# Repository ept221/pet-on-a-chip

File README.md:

# Pet On A Chip
Pet on a chip is a project which condenses the control logic the robot described in Frank DaCosta's book "How to Build Your Own Working Robot Pet" onto a single FPGA. More details, pictures, and videos can be found on this [blog post](https://ezrasrobots.wordpress.com/2021/07/07/pet-on-a-chip/).

## tinySoC
tinySoC is a small system on a chip responsible for controlling the robot. It consists of an 8-bit CPU, an 80 column VGA graphics controller, a programmable interrupt controller, GPIO, counter/timer peripherals, dual closed loop motor controllers, a servo controller, a sonar controller, and a UART, all implemented on an iCE40 FPGA. It also comes with an assembler and utilities for loading programs into the chip's internal block memory without having to rerun synthesis and place-and-route.

## The CPU

The CPU is an 8-bit RISC core, with a Harvard architecture. It has a 16-bit wide instruction memory, an 8-bit wide data memory, and both have a 16-bit address. The CPU has 16 general purpose 8-bit registers along with a 4-bit status register. The processor is not fully pipelined, but does fetch the next instruction while executing the current one. Most instructions execute in a single clock cycle, but a few take two or three.

## The GPU

The GPU operates in a monochrome 80 column text mode, and outputs a VGA signal at a resolution of 640 by 480 at 60 frames per second. The GPU contains an ASCII buffer which the user can write to in order to display messages on the screen. A control register allows the user to set the text to one of 7 colors, and to enable an interrupt to the CPU which fires every time a frame finishes and enters the blanking period. Not shown in the diagram is control logic that allows the screen to be scrolled upwards by writing to the control register.

## The Instruction Set

## The PCBs
The main board:

The expantion board:

## The Assembler

The assembler is case insensitive.

### Comments
Comments begin with semicolons.
```assembly
        .code
        ldi r0, 1 ; This is a comment
```

### Constants
Constants are in decimal by default, but hexadecimal and binary are also supported. Constants can also be negative and are stored in two's complement form when assembled. Chars can also be entered as constants.
```assembly
        .code
        ldi r0, 10     ; Decimal constant
        ldi r0, 0x0A   ; Hexadecimal constant
        ldi r0, 0b1010 ; Binary constant
        ldi r0, -10    ; A negative constant
        ldi r0, 'a'    ; A char constant
        ldi r0, '\n'   ; An escaped char constant
```

### Label Definitions
Label definitions may be any string ending with a colon, as long as the string is not in the form of a constant or is one of the reserved keywords

```assembly
        .code
        ldi r0, 10
loop:   adi r0, -1
        bnz loop
        hlt
```

### Directives

#### .code
Specifies that the following lines are code to be assembled and placed in instruction memory.

#### .data
Specifies that the following lines are data to be placed in data memory.

#### .org
Sets the origin to the given address. Only forward movement of the origin is permitted.
```assembly
        .code
        ldi r0, 1
        out r0, 0
        br foo
        
        .org 0x0B
foo:    out r0, 1
        hlt

;*************************************************************************
; Assembles to the following:
; Address        Label          Code                     Source
; ------------------------------------------------------------------------
; 0x0000                        0b0000000000010001       LDI R0, 1        
; 0x0001                        0b0000000000001001       OUT R0, 0        
; 0x0002                        0b0000000010011110       BR FOO           
; 0x000B         FOO:           0b0000000000011001       OUT R0, 1        
; 0x000C                        0b1111111111111111       HLT 
```

#### .db
Writes one or more data bytes sequentially into data memory.
```assembly
        .data
        .db 0x01, 0x44, 0x73

;*************************************************************************
; Assembles to the following:
; Address        Label          Data
; ------------------------------------------
; 0x0000                        0x01
; 0x0001                        0x44
; 0x0002                        0x73
```

#### .ds
Defines a block of space in the data memory. This is useful for allocating room for a buffer.
```assembly
        .data
        .db 5
        .ds 3
        .db 7

;*************************************************************************
; Assembles to the following:
; Address        Label          Data
; ------------------------------------------
; 0x0000                        0x05                                         
; 0x0004                        0x07 
```

#### .string
Writes a null terminated ASCII string into data memory. Double quotes and backslashes must be escaped with a backslash.

```assembly
        .data
        .string "The robot says \"Hi!\""
        
;*************************************************************************
; Assembles to the following:
; Address        Label          Data
; ------------------------------------------
; 0x0000                        0x54
; 0x0001                        0x68
; 0x0002                        0x65
; 0x0003                        0x20
; 0x0004                        0x72
; 0x0005                        0x6F
; 0x0006                        0x62
; 0x0007                        0x6F
; 0x0008                        0x74
; 0x0009                        0x20
; 0x000A                        0x73
; 0x000B                        0x61
; 0x000C                        0x79
; 0x000D                        0x73
; 0x000E                        0x20
; 0x000F                        0x22
; 0x0010                        0x48
; 0x0011                        0x69
; 0x0012                        0x21
; 0x0013                        0x22
; 0x0014                        0x00
```

#### .ostring
Write a ASCII string into data memory. The string is open, which means that it is not null terminated. This is useful if you have a long string that you want to split up into multiple lines in the assembly source file.

```assembly
        .data
        .ostring "Hi! "
        .string  "Bye!"

;*************************************************************************
; Assembles to the following:
; Address        Label          Data
; ------------------------------------------
; 0x0000                        0x48
; 0x0001                        0x69
; 0x0002                        0x21
; 0x0003                        0x20
; 0x0004                        0x42
; 0x0005                        0x79
; 0x0006                        0x65
; 0x0007                        0x21
; 0x0008                        0x00
```

#### .define
Equates a symbol with a number.
```assembly
        .code
        .define foo, 5
        ldi r0, foo
        hlt
        
;*************************************************************************
; Assembles to the following:        
; Address        Label          Code                     Source
; ------------------------------------------------------------------------
; 0x0000                        0b0000000001010001       LDI R0, FOO     
; 0x0001                        0b0000000011110000       HLT  
```

### Expressions
Any time an instruction or directive requires a numerical argument, an expression can be used.
Supported operations inside expressions include addition and subtraction. The location counter $ is also made available. If an instruction is two bytes long then $ refers to the address of the second byte. Expressions may contain symbols, but must resolve within two passes of the assembler, and if used for directive arguments, must resolve in a single pass.

```assembly
; Example resolution in one pass
        .code
        .define foo, 5
        ldi r0, foo + 7
        hlt

;*************************************************************************
; Assembles to the following:
; Address        Label          Code                     Source
; ------------------------------------------------------------------------
; 0x0000                        0b0000000011000001       LDI R0, FOO + 7
; 0x0001                        0b0000000011110000       HLT
```
```assembly
; Example resolution in two passes
        .code
        ldi r0, foo + 7
        hlt
        .define foo, 5

;*************************************************************************
; Assembles to the following:
; Address        Label          Code                     Source
; ------------------------------------------------------------------------
; 0x0000                        0b0000000011000001       LDI R0, FOO + 7
; 0x0001                        0b0000000011110000       HLT
```
```assembly
; Example resolution in two passes with $
        .code
        ldi r0, $
        jmp $ + foo
        .define foo, 2
        nop
        nop
        nop
        hlt

;*************************************************************************
; Assembles to the following:
; Address        Label          Code                     Source
; ------------------------------------------------------------------------
; 0x0000                        0b0000000000000001       LDI R0, $
; 0x0001                        0b0000000010111000       JMP $ + FOO
; 0x0002                        0b0000000000000100
; 0x0003                        0b0000000000000000       NOP
; 0x0004                        0b0000000000000000       NOP
; 0x0005                        0b0000000000000000       NOP
; 0x0006                        0b0000000011110000       HLT
```
## The Development Process
To perform synthesis and place-and-route, run:
```bash
make synth
make pnr
```
To assemble a demo program, run:
```bash
./assemble programs/shell.asm shell
```
To upload the configuration bitstream for the previously assembled program, run:
```bash
./upload shell
```
You will now be able to interact with a basic shell over the UART at 115200 baud. Additionally, the output will also be sent over the VGA interface.

## Requirements
- Yosys for synthisis
- nextpnr for place and route
- icestorm tools for icebram and iceprog

## Peripherals

There are a variety of memory mapped peripherals included in the system. The memory map is configured in `soc/src/d_ram_and_io/d_ram_and_io.v`. Currently addresses `0x0000` to `0x07FF` are mapped to data ram. The peripherals are mapped from `0x1000` to `0x10FF`. The instructions `in` and `out` are designed to allow for quickly and easily reading and writing to peripherals within this address range. For example, `out r1, 5` writes the value in r1 to address `0x1005`. In contrast, when reading and writing to data memory, or writing to the graphics buffer which is from `0x2000` to `0x2960`, `in` and `out` cannot be used, and the other load and store instructions must be used instead, which require setting up a pointer in a register pair to the memory location you want to operate on.

### GPIO
|Address|Register|r/w|Description|
|-------|--------|---|-----------|
|0x1000|Direction|r/w|Sets GPIO pins to input or output|
|0x1001|Port|r/w|Write values to be outputed|
|0x1002|Pin|r|Read values on pins|

### Counter Timer
|Address|Register|r/w|Description|
|-------|--------|---|-----------|
|0x1003| Scale LSB|r/w||
|0x1004| Scale MSB|r/w||
|0x1005| Control|r/w||
|0x1006| CMPR0|r/w||
|0x1007| CMPR1|r/w||
|0x1008| Counter|r||

### UART
|Address|Register|r/w|Description|
|-------|--------|---|-----------|
|0x1009| Baud|r/w| Configures the baudrate|
|0x100A| Status|r| Signals empty tx buffer and or full rx buffer|
|0x100B| Buffer |r/w| Write to tx buffer, read from rx buffer|

### Motor Controller
|Address|Register|r/w|Description|
|-------|--------|---|-----------|
|0x100C| Control |r/w| Sets the motors' directions|
|0x100D| Enable  |r/w| Enables the motor driver|
|0x100E| Speed 0 |r/w| Target speed of motor 0|
|0x100F| Speed 1 |r/w| Target speed of motor 1|
|0x1010| RPM 0 |r| Actual speed of motor 0|
|0x1011| RPM 1 |r| Actual speed of motor 1|

### Servo Controller
|Address|Register|r/w|Description|
|-------|--------|---|-----------|
|0x1012| Position|r/w| Sets the position of the servo|

### Sonar Controller
|Address|Register|r/w|Description|
|-------|--------|---|-----------|
|0x1013| Status | r| Signals new reading in range register |
|0x1014| Range | r| Holds the measured distance|

### Programmable Interrupt Controller
|Address|Register|r/w|Description|
|-------|--------|---|-----------|
|0x1015| Vect 0 Low|r/w| LSBs of interrupt vector 0|
|0x1016| Vect 0 High|r/w| MSBs of interrupt vector 0|
|0x1017| Vect 1 Low|r/w| LSBs of interrupt vector 1|
|0x1018| Vect 1 High|r/w| MSBs of interrupt vector 1|
|0x1019| Vect 2 Low|r/w| LSBs of interrupt vector 2|
|0x101A| Vect 2 High|r/w| MSBs of interrupt vector 2|
|0x101B| Vect 3 Low|r/w| LSBs of interrupt vector 3|
|0x101C| Vect 3 High|r/w| MSBs of interrupt vector 3|

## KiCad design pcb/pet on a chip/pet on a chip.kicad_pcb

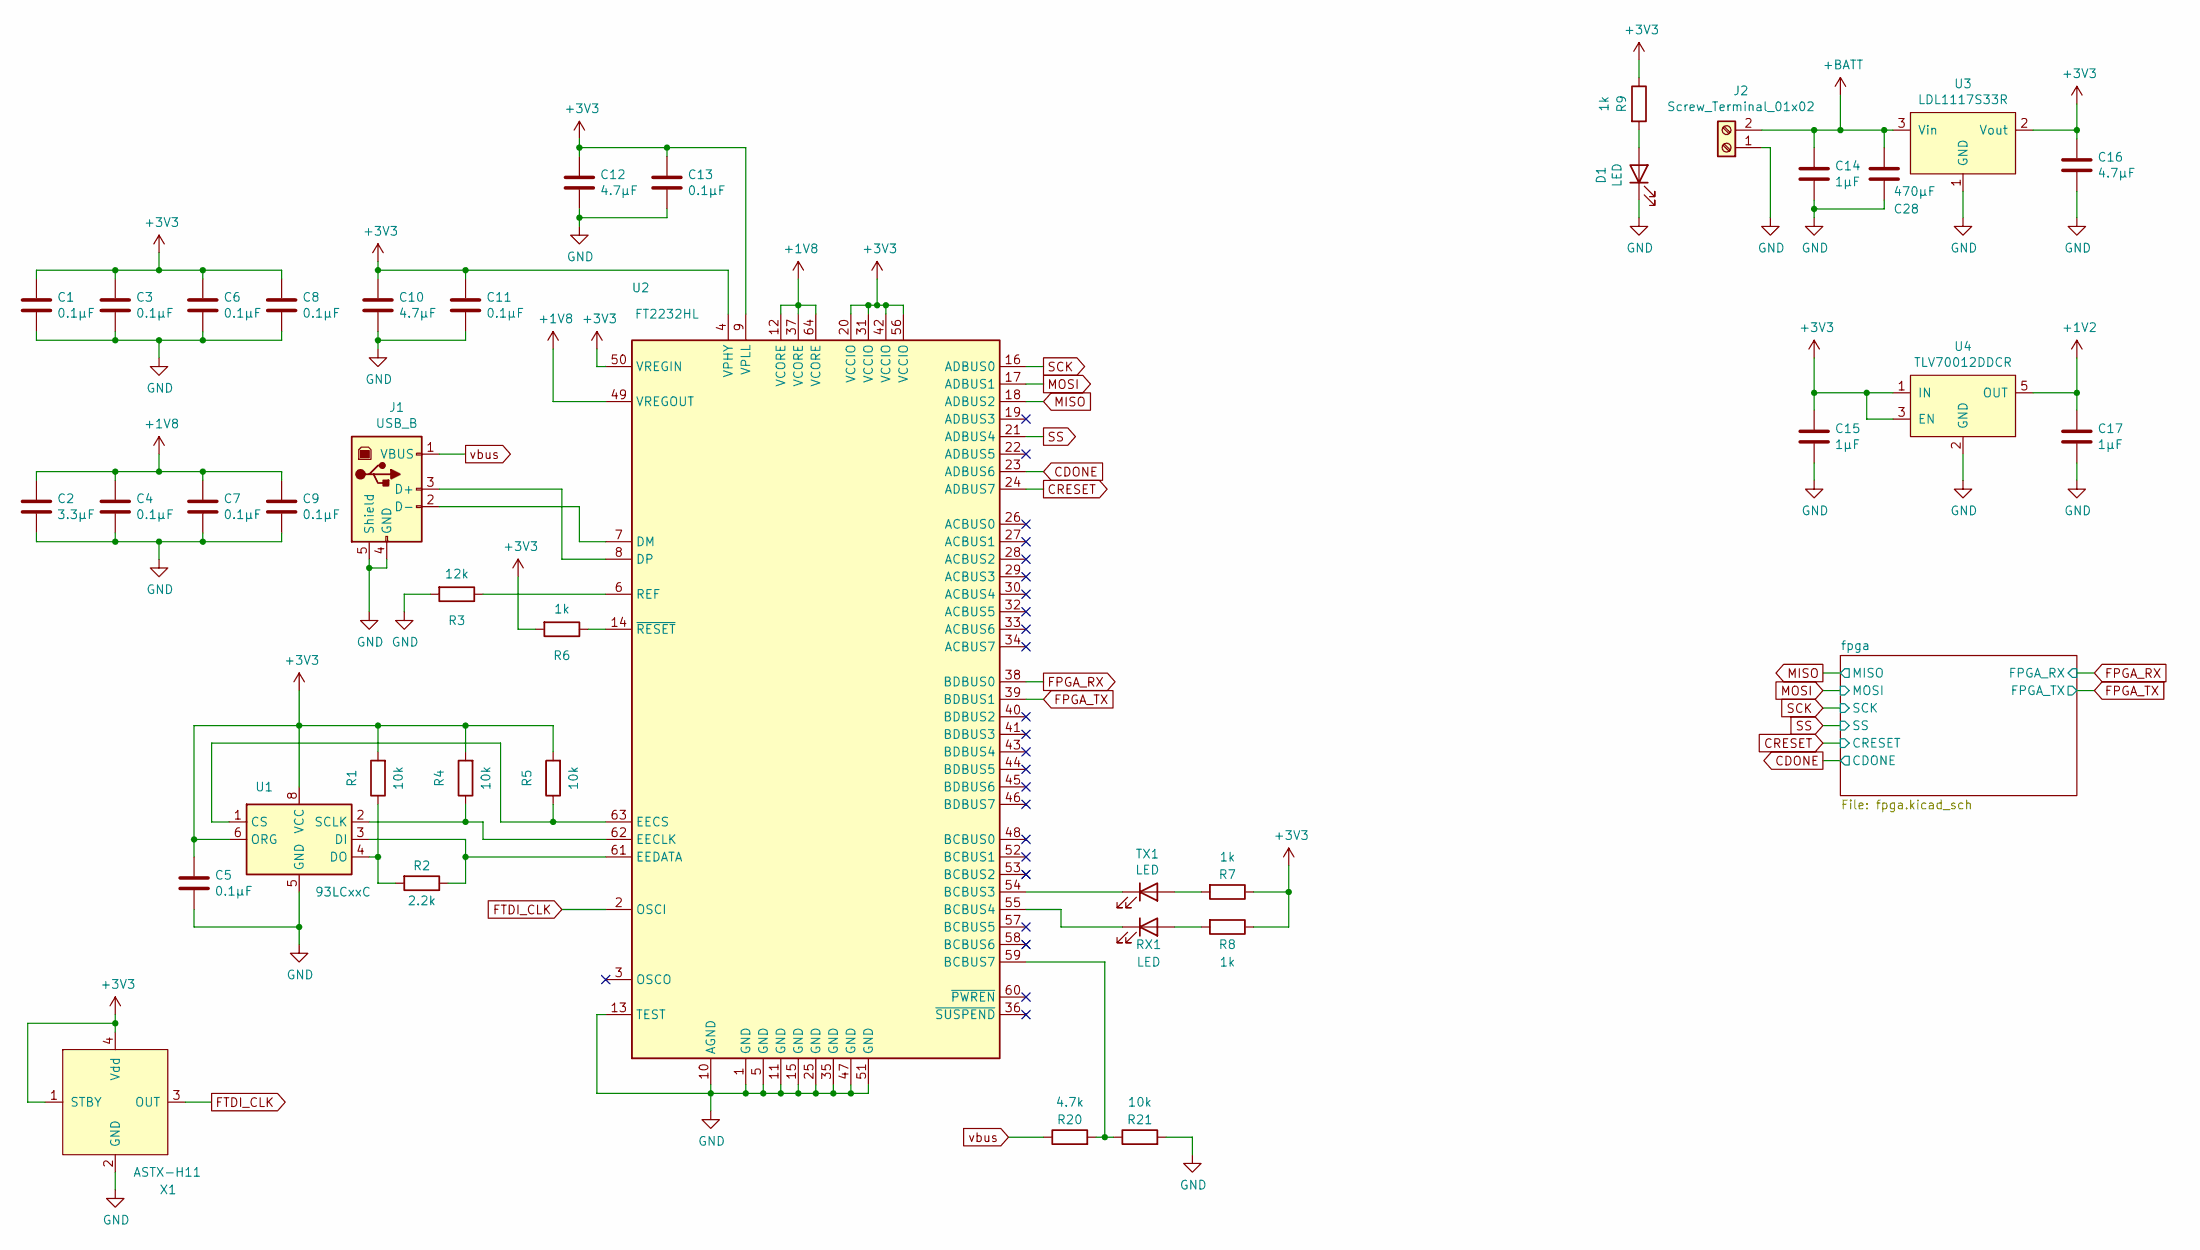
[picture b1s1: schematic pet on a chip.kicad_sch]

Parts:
C1, C3, C4, C5, C6, C7, C8, C9, C11, C13: 0.1µF; C_0603_1608Metric
C2: 3.3µF; C_0603_1608Metric
C10, C12, C16: 4.7µF; C_0603_1608Metric
C14, C15, C17: 1µF; C_0603_1608Metric
C28: 470µF; CP_Elec_6.3x7.7
D1: LED; R_0603_1608Metric
J1: USB_B; USB_B_OST_USB-B1HSxx_Horizontal
J2: Screw_Terminal_01x02; TerminalBlock_4Ucon_1x02_P3.50mm_Horizontal
R1, R4, R5, R21: 10k; R_0603_1608Metric
R2: 2.2k; R_0603_1608Metric
R3: 12k; R_0603_1608Metric
R6, R7, R8, R9: 1k; R_0603_1608Metric
R20: 4.7k; R_0603_1608Metric
RX1: LED; R_0603_1608Metric
TX1: LED; R_0603_1608Metric
U1: 93LCxxC; SOIC-8_3.9x4.9mm_P1.27mm
U2: FT2232HL; LQFP-64_10x10mm_P0.5mm
U3: LDL1117S33R; SOT-223-3_TabPin2
U4: TLV70012DDCR; SOT-23-5
X1: ASTX-H11; Oscillator_SMD_Abracon_ASE-4Pin_3.2x2.5mm

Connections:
+1V2: C17.1, U4.5 (OUT); also elsewhere on the board
+1V8: C2.1, C4.1, C7.1, C9.1, U2.12 (VCORE), U2.37 (VCORE), U2.49 (VREGOUT), U2.64 (VCORE)
+3V3: C1.1, C3.1, C5.1, C6.1, C8.1, C10.1, C11.1, C12.1, C13.1, C15.1, C16.1, R1.2, R4.2, R5.2, R6.2, R7.1, R8.1, R9.1, U1.6 (ORG), U1.8 (VCC), U2.4 (VPHY), U2.9 (VPLL), U2.20 (VCCIO), U2.31 (VCCIO), U2.42 (VCCIO), U2.50 (VREGIN), U2.56 (VCCIO), U3.2 (Vout), U4.1 (IN), U4.3 (EN), X1.1 (STBY), X1.4 (Vdd); also elsewhere on the board
+BATT: C14.1, C28.1, J2.2, U3.3 (Vin); also elsewhere on the board
CDONE: U2.23 (ADBUS6); also elsewhere on the board
CRESET: U2.24 (ADBUS7); also elsewhere on the board
FPGA_RX: U2.38 (BDBUS0); also elsewhere on the board
FPGA_TX: U2.39 (BDBUS1); also elsewhere on the board
FTDI_CLK: U2.2 (OSCI), X1.3 (OUT)
GND: C1.2, C2.2, C3.2, C4.2, C5.2, C6.2, C7.2, C8.2, C9.2, C10.2, C11.2, C12.2, C13.2, C14.2, C15.2, C16.2, C17.2, C28.2, D1.1 (K), J1.4 (GND), J1.5 (Shield), J2.1, R3.2, R21.2, U1.5 (GND), U2.1 (GND), U2.5 (GND), U2.10 (AGND), U2.11 (GND), U2.13 (TEST), U2.15 (GND), U2.25 (GND), U2.35 (GND), U2.47 (GND), U2.51 (GND), U3.1 (GND), U4.2 (GND), X1.2 (GND); also elsewhere on the board
MISO: U2.18 (ADBUS2); also elsewhere on the board
MOSI: U2.17 (ADBUS1); also elsewhere on the board
unnamed: D1.2 (A), R9.2
unnamed: J1.2 (D-), U2.7 (DM)
unnamed: J1.3 (D+), U2.8 (DP)
unnamed: R1.1, R2.2, U1.4 (DO)
unnamed: R2.1, U1.3 (DI), U2.61 (EEDATA)
unnamed: R3.1, U2.6 (REF)
unnamed: R4.1, U1.2 (SCLK), U2.62 (EECLK)
unnamed: R5.1, U1.1 (CS), U2.63 (EECS)
unnamed: R6.1, U2.14 (~RESET)
unnamed: R7.2, TX1.2 (A)
unnamed: R8.2, RX1.2 (A)
unnamed: R20.2, R21.1, U2.59 (BCBUS7)
unnamed: RX1.1 (K), U2.55 (BCBUS4)
unnamed: TX1.1 (K), U2.54 (BCBUS3)
SCK: U2.16 (ADBUS0); also elsewhere on the board
SS: U2.21 (ADBUS4); also elsewhere on the board
vbus: J1.1 (VBUS), R20.1

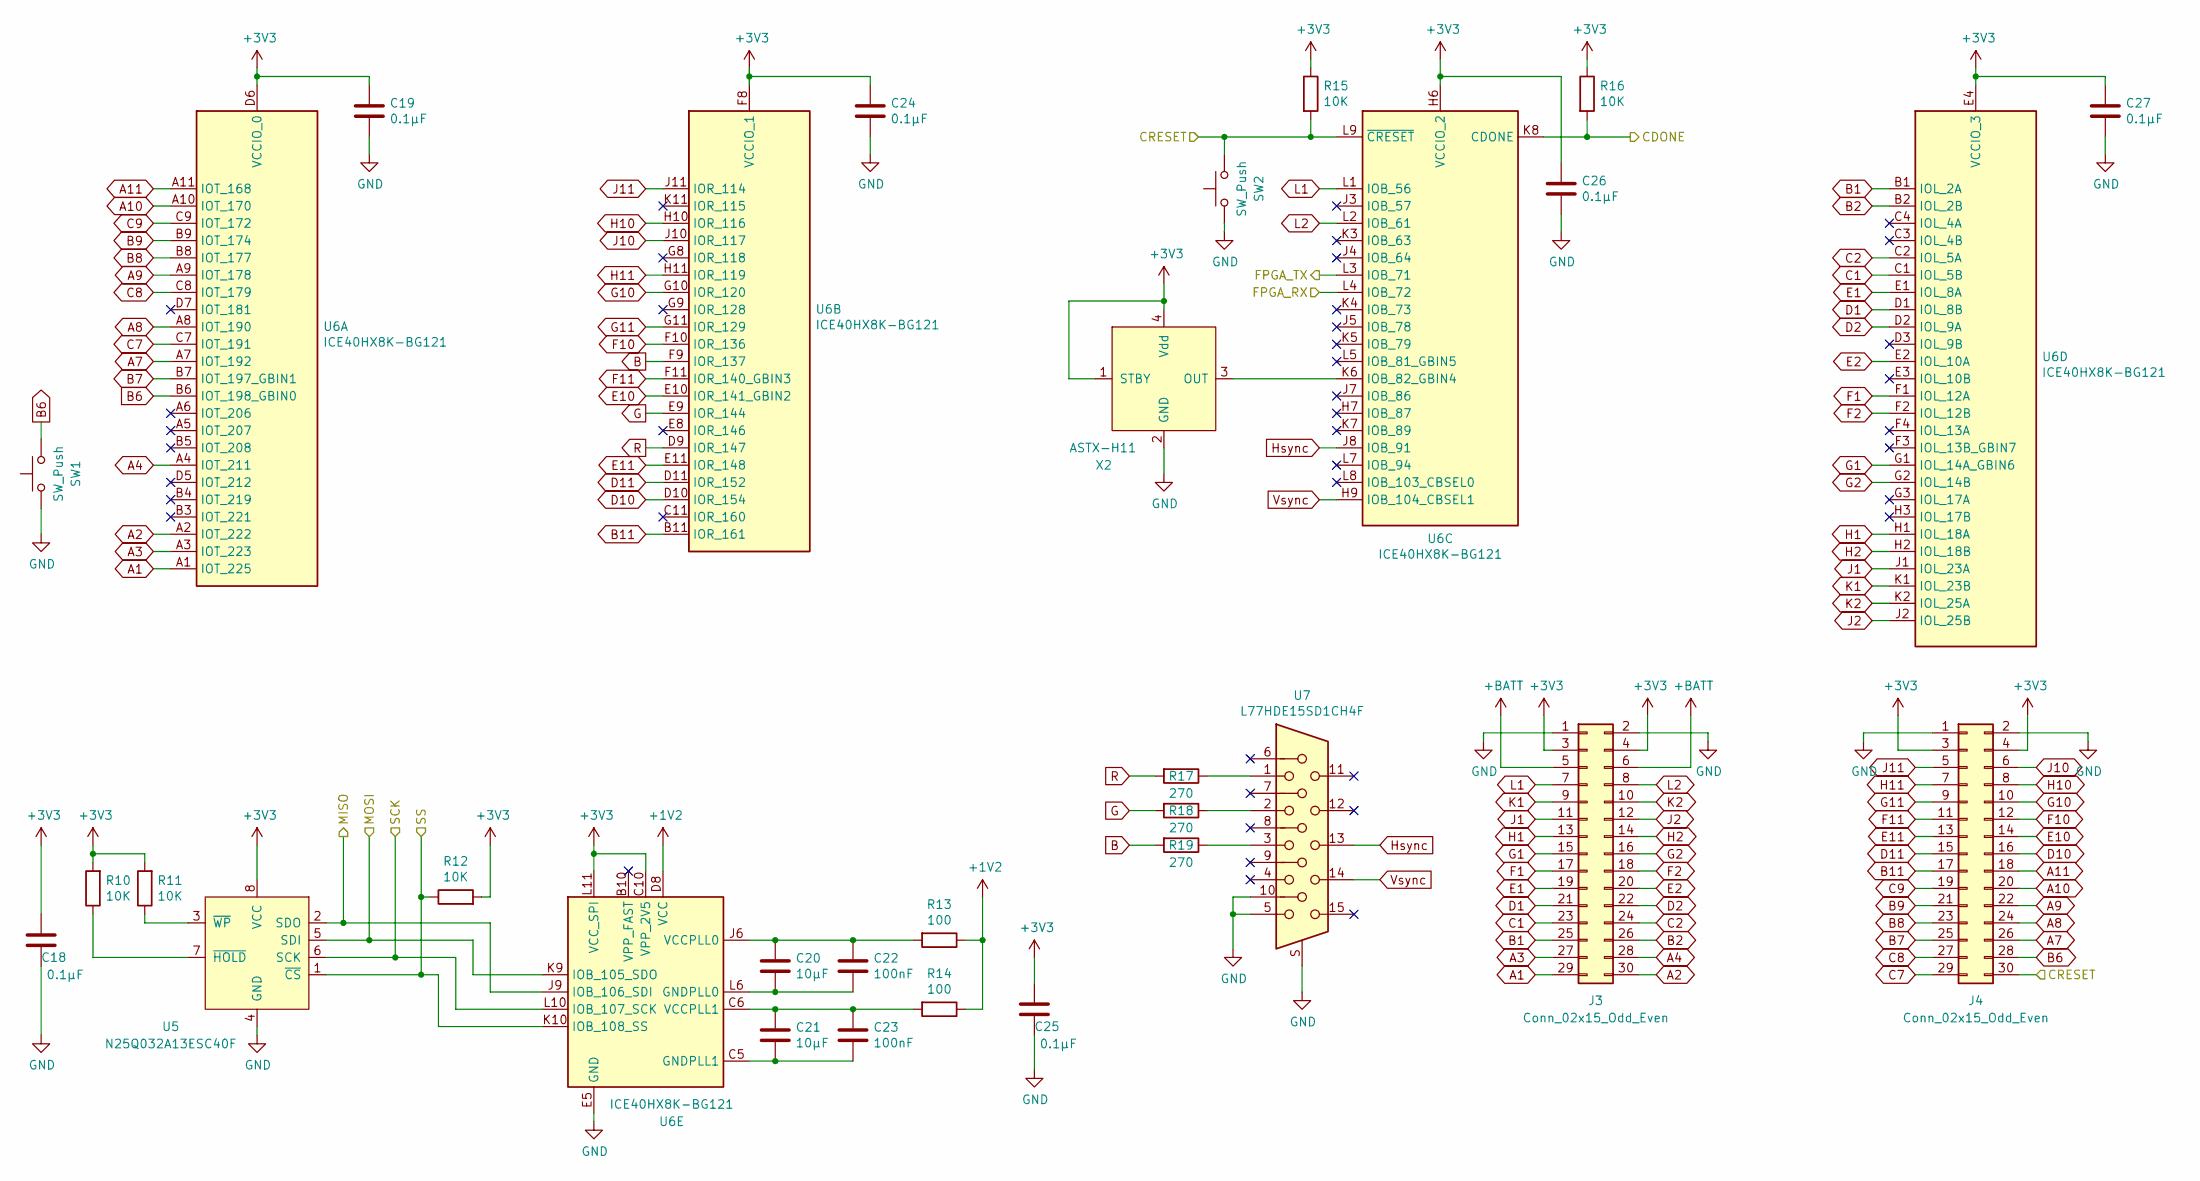
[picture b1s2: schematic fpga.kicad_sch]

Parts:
C18, C19, C24, C25, C26, C27: 0.1µF; C_0603_1608Metric
C20, C21: 10µF; C_0603_1608Metric
C22, C23: 100nF; C_0603_1608Metric
J3, J4: Conn_02x15_Odd_Even; PinHeader_2x15_P2.54mm_Vertical
R10, R11, R12, R15, R16: 10K; R_0603_1608Metric
R13, R14: 100; R_0603_1608Metric
R17, R18, R19: 270; R_0603_1608Metric
SW1, SW2: SW_Push; SW_PUSH_6mm
U5: N25Q032A13ESC40F; SOP-8_3.9x4.9mm_P1.27mm
U6: ICE40HX8K-BG121; BGA-121_9.0x9.0mm_Layout11x11_P0.8mm_Ball0.4mm_Pad0.35mm_NS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
U7: L77HDE15SD1CH4F; AMPHENOL_L77HDE15SD1CH4F
X2: ASTX-H11; Oscillator_SMD_Abracon_ASE-4Pin_3.2x2.5mm

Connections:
+1V2: R13.1, R14.1, U6.D4 (VCC), U6.D8 (VCC), U6.H4 (VCC), U6.H8 (VCC); also elsewhere on the board
+3V3: C18.2, C19.1, C24.1, C25.2, C26.1, C27.1, J3.3, J3.4, J4.3, J4.4, R10.2, R11.2, R12.2, R15.1, R16.1, U5.8 (VCC), U6.C10 (VPP_2V5), U6.D6 (VCCIO_0), U6.E4 (VCCIO_3), U6.F8 (VCCIO_1), U6.G4 (VCCIO_3), U6.H6 (VCCIO_2), U6.L11 (VCC_SPI), X2.1 (STBY), X2.4 (Vdd); also elsewhere on the board
+BATT: J3.5, J3.6; also elsewhere on the board
A1: J3.29, U6.A1 (IOT_225)
A2: J3.30, U6.A2 (IOT_222)
A3: J3.27, U6.A3 (IOT_223)
A4: J3.28, U6.A4 (IOT_211)
A7: J4.26, U6.A7 (IOT_192)
A8: J4.24, U6.A8 (IOT_190)
A9: J4.22, U6.A9 (IOT_178)
A10: J4.20, U6.A10 (IOT_170)
A11: J4.18, U6.A11 (IOT_168)
B: R19.2, U6.F9 (IOR_137)
B1: J3.25, U6.B1 (IOL_2A)
B2: J3.26, U6.B2 (IOL_2B)
B6: J4.28, SW1.2, U6.B6 (IOT_198_GBIN0)
B7: J4.25, U6.B7 (IOT_197_GBIN1)
B8: J4.23, U6.B8 (IOT_177)
B9: J4.21, U6.B9 (IOT_174)
B11: J4.17, U6.B11 (IOR_161)
C1: J3.23, U6.C1 (IOL_5B)
C2: J3.24, U6.C2 (IOL_5A)
C7: J4.29, U6.C7 (IOT_191)
C8: J4.27, U6.C8 (IOT_179)
C9: J4.19, U6.C9 (IOT_172)
CDONE: R16.2, U6.K8 (CDONE); also elsewhere on the board
CRESET: J4.30, R15.2, SW2.2, U6.L9 (~CRESET); also elsewhere on the board
D1: J3.21, U6.D1 (IOL_8B)
D2: J3.22, U6.D2 (IOL_9A)
D10: J4.16, U6.D10 (IOR_154)
D11: J4.15, U6.D11 (IOR_152)
E1: J3.19, U6.E1 (IOL_8A)
E2: J3.20, U6.E2 (IOL_10A)
E10: J4.14, U6.E10 (IOR_141_GBIN2)
E11: J4.13, U6.E11 (IOR_148)
F1: J3.17, U6.F1 (IOL_12A)
F2: J3.18, U6.F2 (IOL_12B)
F10: J4.12, U6.F10 (IOR_136)
F11: J4.11, U6.F11 (IOR_140_GBIN3)
FPGA_RX: U6.L4 (IOB_72); also elsewhere on the board
FPGA_TX: U6.L3 (IOB_71); also elsewhere on the board
G: R18.2, U6.E9 (IOR_144)
G1: J3.15, U6.G1 (IOL_14A_GBIN6)
G2: J3.16, U6.G2 (IOL_14B)
G10: J4.10, U6.G10 (IOR_120)
G11: J4.9, U6.G11 (IOR_129)
GND: C18.1, C19.2, C24.2, C25.1, C26.2, C27.2, J3.1, J3.2, J4.1, J4.2, SW1.1, SW2.1, U5.4 (GND), U6.E5 (GND), U6.E6 (GND), U6.E7 (GND), U6.F5 (GND), U6.F6 (GND), U6.F7 (GND), U6.G5 (GND), U6.G6 (GND), U6.G7 (GND), U6.H5 (GND), U7.5, U7.10, U7.S, X2.2 (GND); also elsewhere on the board
H1: J3.13, U6.H1 (IOL_18A)
H2: J3.14, U6.H2 (IOL_18B)
H10: J4.8, U6.H10 (IOR_116)
H11: J4.7, U6.H11 (IOR_119)
Hsync: U6.J8 (IOB_91), U7.13
J1: J3.11, U6.J1 (IOL_23A)
J2: J3.12, U6.J2 (IOL_25B)
J10: J4.6, U6.J10 (IOR_117)
J11: J4.5, U6.J11 (IOR_114)
K1: J3.9, U6.K1 (IOL_23B)
K2: J3.10, U6.K2 (IOL_25A)
L1: J3.7, U6.L1 (IOB_56)
L2: J3.8, U6.L2 (IOB_61)
MISO: U5.2 (SDO), U6.J9 (IOB_106_SDI); also elsewhere on the board
MOSI: U5.5 (SDI), U6.K9 (IOB_105_SDO); also elsewhere on the board
unnamed: C20.1, C22.1, R13.2, U6.J6 (VCCPLL0)
unnamed: C20.2, C22.2, U6.L6 (GNDPLL0)
unnamed: C21.1, C23.1, R14.2, U6.C6 (VCCPLL1)
unnamed: C21.2, C23.2, U6.C5 (GNDPLL1)
unnamed: R10.1, U5.7 (~HOLD)
unnamed: R11.1, U5.3 (~WP)
unnamed: R17.1, U7.1
unnamed: R18.1, U7.2
unnamed: R19.1, U7.3
unnamed: U6.K6 (IOB_82_GBIN4), X2.3 (OUT)
R: R17.2, U6.D9 (IOR_147)
SCK: U5.6 (SCK), U6.L10 (IOB_107_SCK); also elsewhere on the board
SS: R12.1, U5.1 (~CS), U6.K10 (IOB_108_SS); also elsewhere on the board
Vsync: U6.H9 (IOB_104_CBSEL1), U7.14

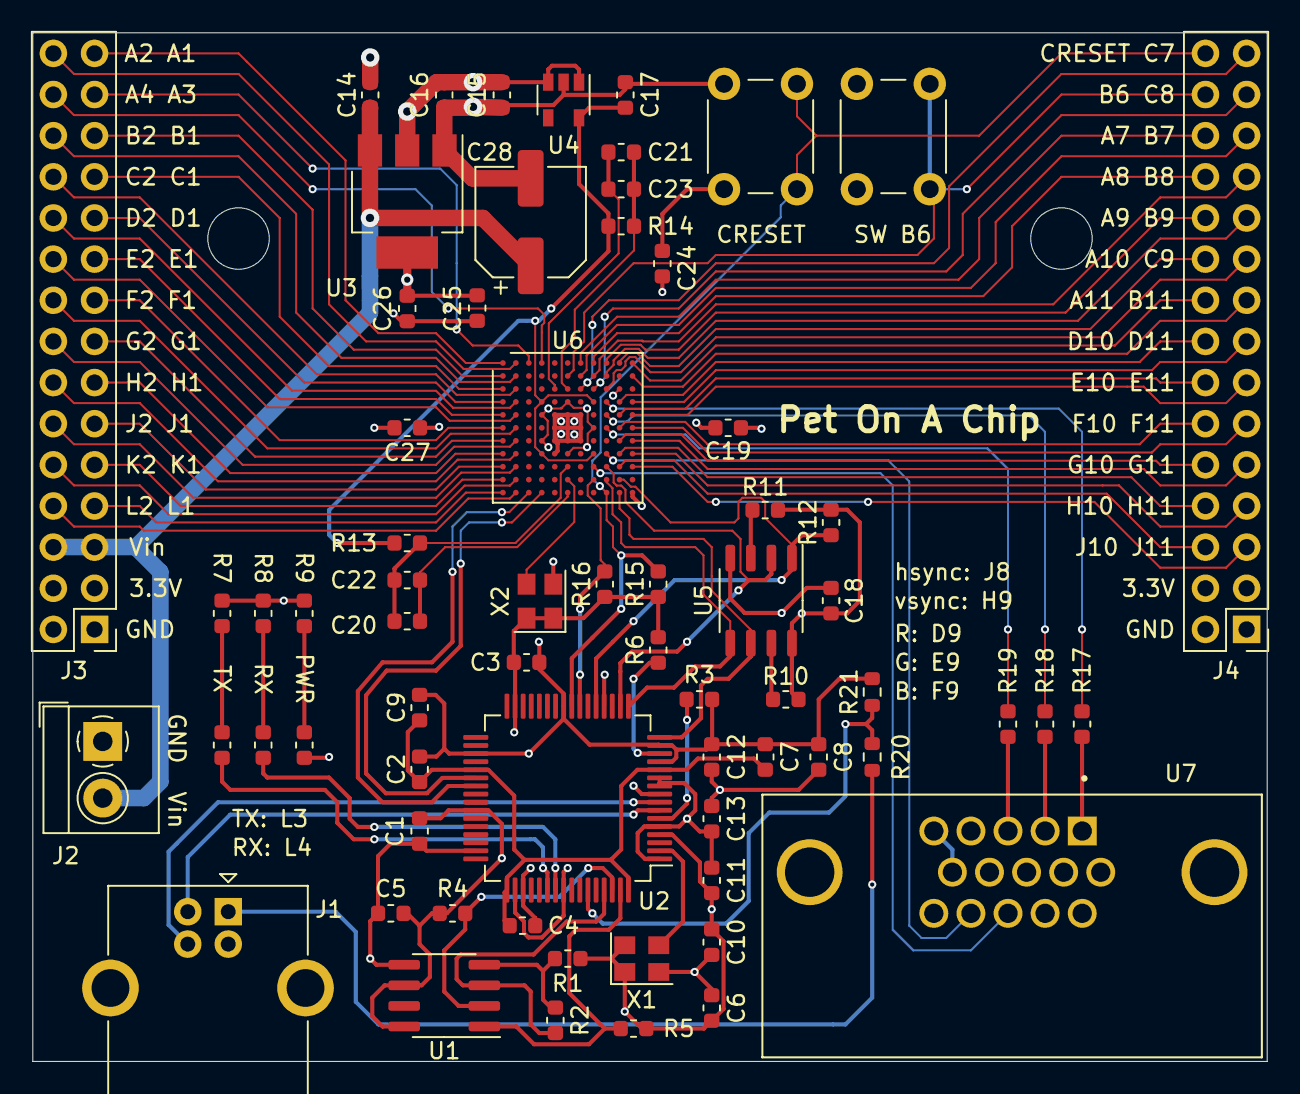
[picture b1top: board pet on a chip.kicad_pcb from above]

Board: 4 copper layers, 76.2 x 63.5 mm, 67 parts (0 on the bottom side), 93 nets.

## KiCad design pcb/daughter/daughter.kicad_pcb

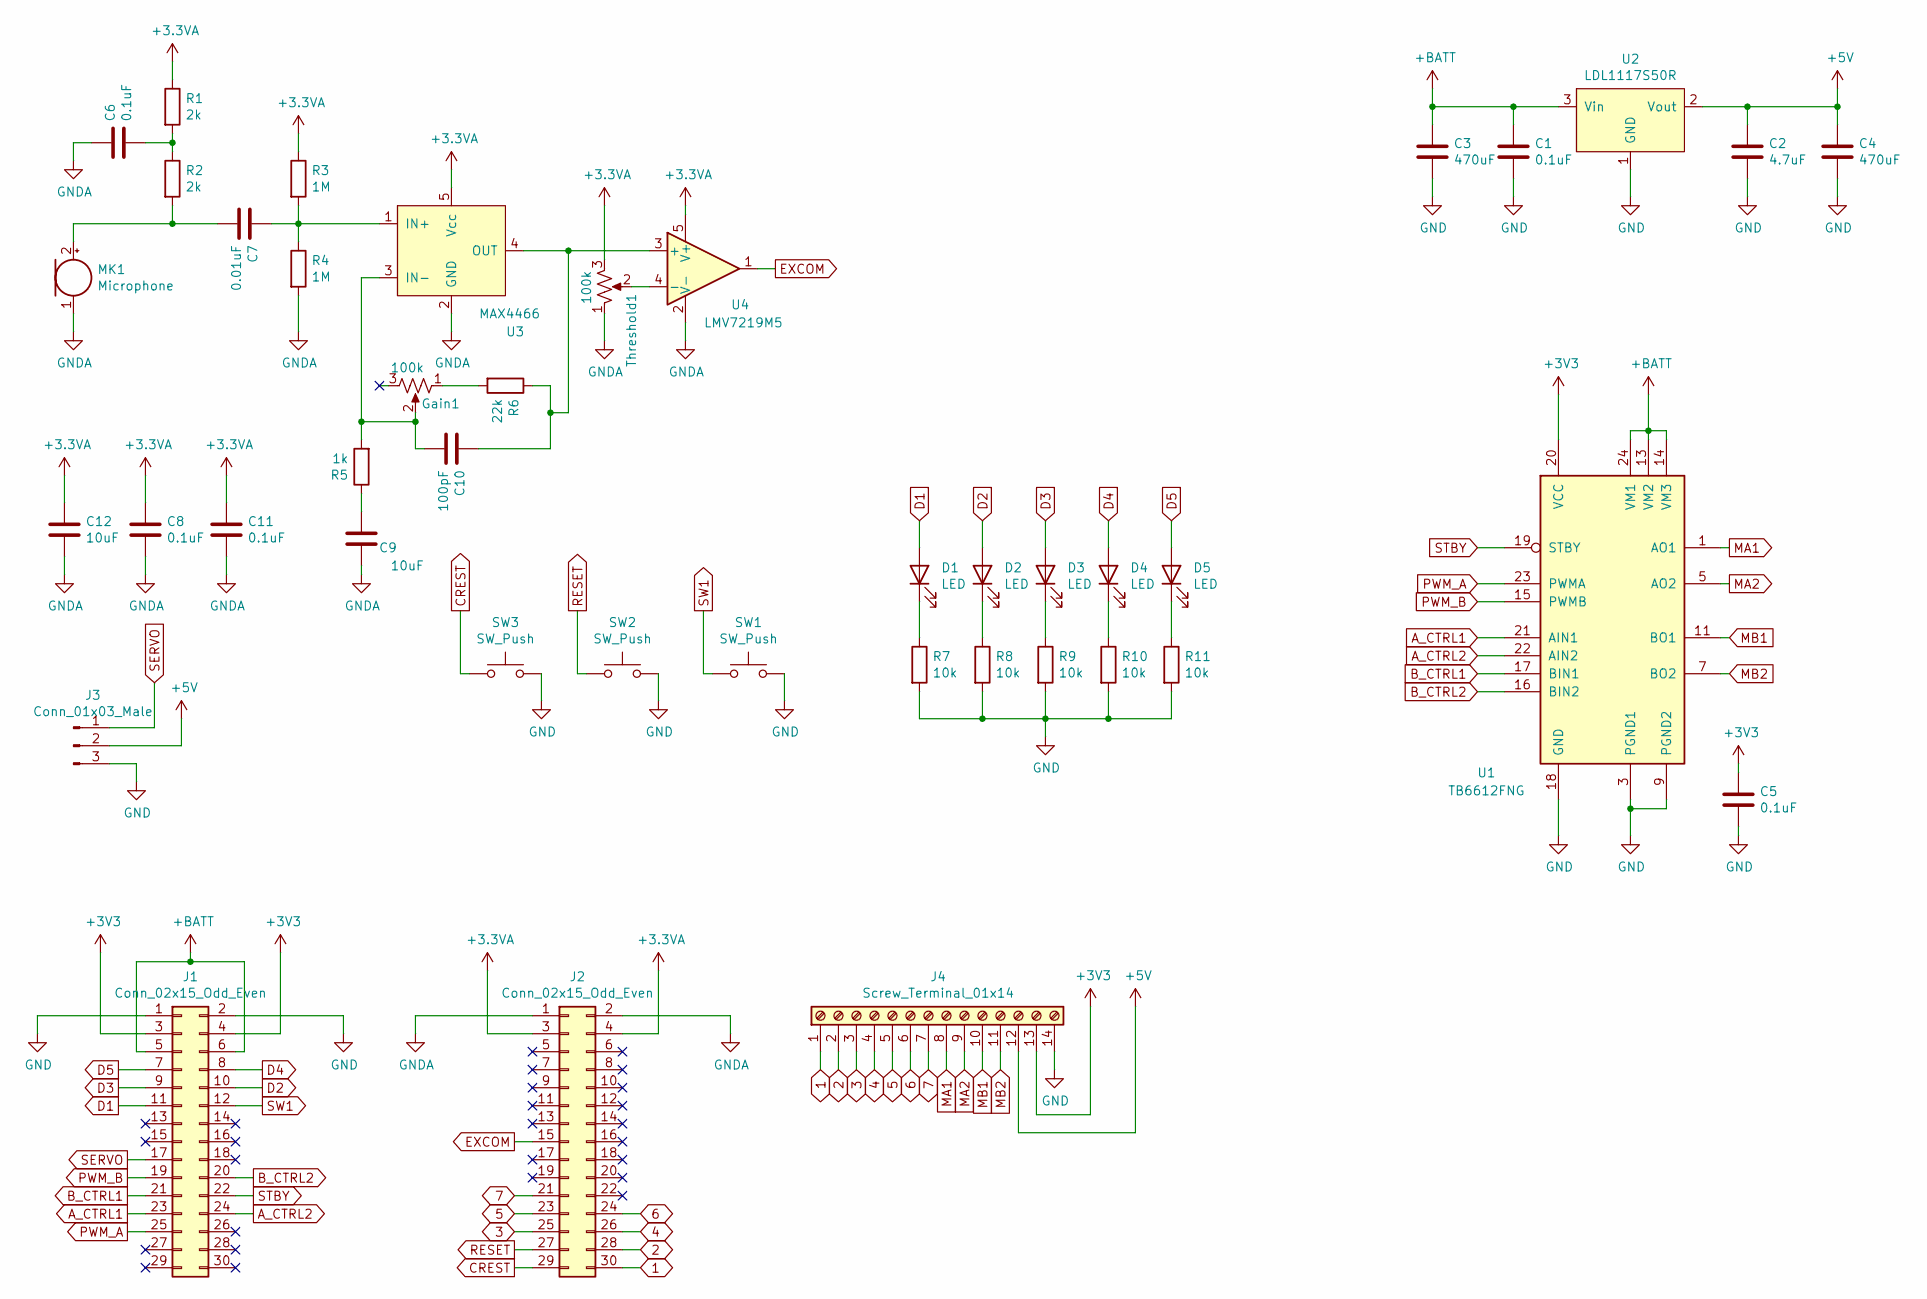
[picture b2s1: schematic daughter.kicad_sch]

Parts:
C1, C5, C6, C8, C11: 0.1uF; C_0603_1608Metric
C2: 4.7uF; C_0603_1608Metric
C3, C4: 470uF; CP_Elec_6.3x7.7
C7: 0.01uF; C_0603_1608Metric
C9, C12: 10uF; C_0603_1608Metric
C10: 100pF; C_0603_1608Metric
D1, D2, D3, D4, D5: LED; LED_0603_1608Metric
Gain1: 100k; Potentiometer_Bourns_3314J_Vertical
J1, J2: Conn_02x15_Odd_Even; PinHeader_2x15_P2.54mm_Vertical
J3: Conn_01x03_Male; PinHeader_1x03_P2.54mm_Horizontal
J4: Screw_Terminal_01x14; TerminalBlock_4Ucon_1x14_P3.50mm_Horizontal
MK1: Microphone; MIC_CMA-4544PF-W
R1, R2: 2k; R_0603_1608Metric
R3, R4: 1M; R_0603_1608Metric
R5: 1k; R_0603_1608Metric
R6: 22k; R_0603_1608Metric
R7, R8, R9, R10, R11: 10k; R_0603_1608Metric
SW1, SW2, SW3: SW_Push; SW_PUSH_6mm
Threshold1: 100k; Potentiometer_Bourns_3314J_Vertical
U1: TB6612FNG; SSOP-24_5.3x8.2mm_P0.65mm
U2: LDL1117S50R; SOT-223-3_TabPin2
U3: MAX4466; SOT-23-5
U4: LMV7219M5; SOT-23-5

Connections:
1: J2.30, J4.1
2: J2.28, J4.2
3: J2.25, J4.3
4: J2.26, J4.4
5: J2.23, J4.5
6: J2.24, J4.6
7: J2.21, J4.7
+3.3VA: C8.1, C11.1, C12.1, J2.3, J2.4, R1.1, R3.1, Threshold1.3, U3.5 (Vcc), U4.5 (V+)
+3V3: C5.1, J1.3, J1.4, J4.13, U1.20 (VCC)
+5V: C2.1, C4.1, J3.2, J4.12, U2.2 (Vout)
+BATT: C1.1, C3.1, J1.5, J1.6, U1.13 (VM2), U1.14 (VM3), U1.24 (VM1), U2.3 (Vin)
A_CTRL1: J1.23, U1.21 (AIN1)
A_CTRL2: J1.24, U1.22 (AIN2)
B_CTRL1: J1.21, U1.17 (BIN1)
B_CTRL2: J1.20, U1.16 (BIN2)
CREST: J2.29, SW3.1
D1: D1.2 (A), J1.11
D2: D2.2 (A), J1.10
D3: D3.2 (A), J1.9
D4: D4.2 (A), J1.8
D5: D5.2 (A), J1.7
EXCOM: J2.15, U4.1
GND: C1.2, C2.2, C3.2, C4.2, C5.2, J1.1, J1.2, J3.3, J4.14, R7.2, R8.2, R9.2, R10.2, R11.2, SW1.2, SW2.2, SW3.2, U1.3 (PGND1), U1.4 (PGND1), U1.9 (PGND2), U1.10 (PGND2), U1.18 (GND), U2.1 (GND)
GNDA: C6.1, C8.2, C9.1, C11.2, C12.2, J2.1, J2.2, MK1.1 (-), R4.2, Threshold1.1, U3.2 (GND), U4.2 (V-)
MA1: J4.8, U1.1 (AO1), U1.2 (AO1)
MA2: J4.9, U1.5 (AO2), U1.6 (AO2)
MB1: J4.10, U1.11 (BO1), U1.12 (BO1)
MB2: J4.11, U1.7 (BO2), U1.8 (BO2)
unnamed: C6.2, R1.2, R2.1
unnamed: C7.1, R3.2, R4.1, U3.1 (IN+)
unnamed: C7.2, MK1.2 (+), R2.2
unnamed: C9.2, R5.1
unnamed: C10.1, R6.1, U3.4 (OUT), U4.3 (+)
unnamed: C10.2, Gain1.2, R5.2, U3.3 (IN-)
unnamed: D1.1 (K), R7.1
unnamed: D2.1 (K), R8.1
unnamed: D3.1 (K), R9.1
unnamed: D4.1 (K), R10.1
unnamed: D5.1 (K), R11.1
unnamed: Gain1.1, R6.2
unnamed: Threshold1.2, U4.4 (-)
PWM_A: J1.25, U1.23 (PWMA)
PWM_B: J1.19, U1.15 (PWMB)
RESET: J2.27, SW2.1
SERVO: J1.17, J3.1
STBY: J1.22, U1.19 (STBY)
SW1: J1.12, SW1.1

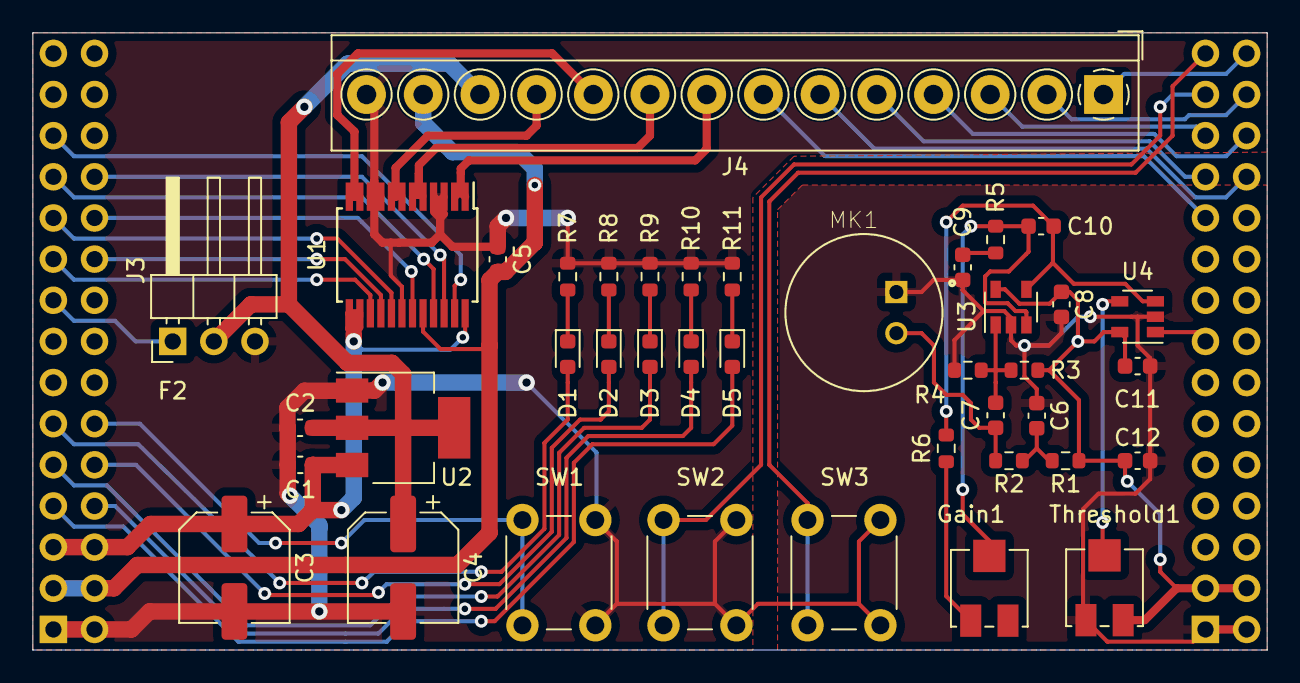
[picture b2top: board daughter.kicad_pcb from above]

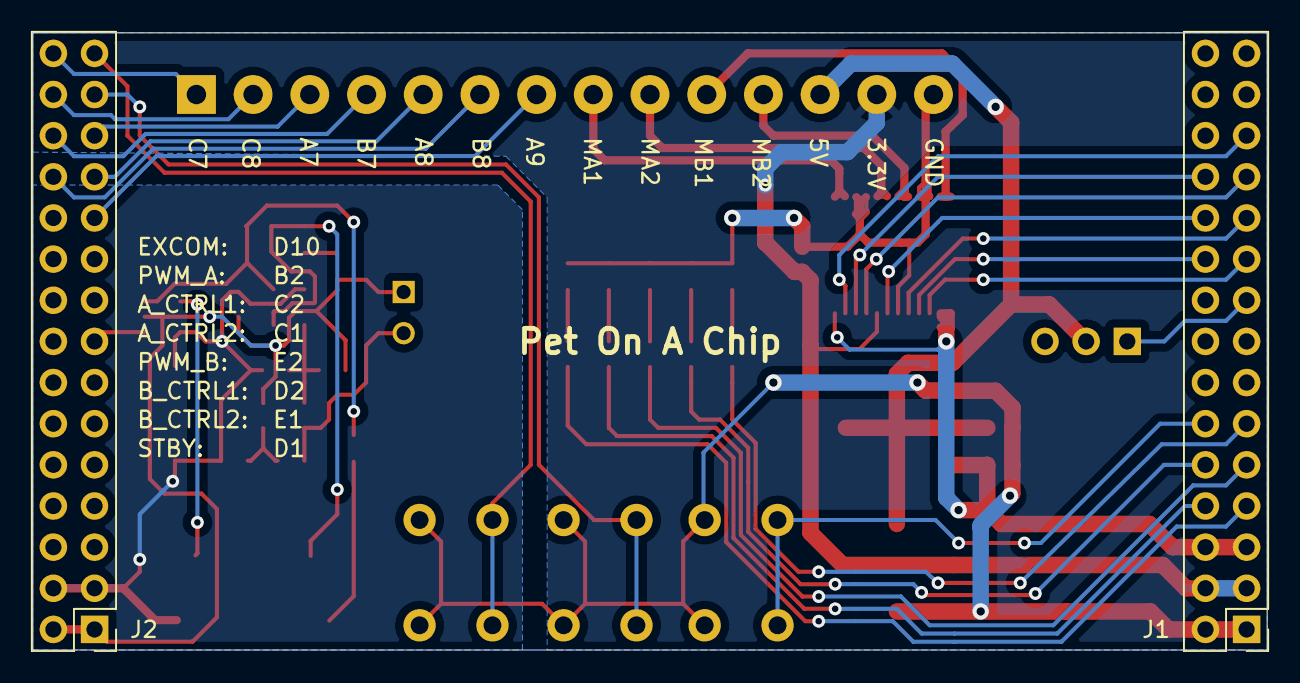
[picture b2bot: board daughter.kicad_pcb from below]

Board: 2 copper layers, 76.2 x 38.1 mm, 42 parts (2 on the bottom side), 47 nets.

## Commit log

2021-04-14 added gerbers
2021-04-14 fixed 3d model paths
2021-04-23 added more docs
2021-04-24 updated cmp and cpi flag convention
2021-04-24 switched from subtract with borrow to subtract with carry. fixed bug in control for pus and pos.
2021-04-24 updated demo programs
2021-04-25 updated shell program
2021-04-25 fixed bugs in shell
2021-04-26 updated shell program and modified uart_io.asm for safty
2021-04-26 assembler can now produce strings without null termination. shell program working.
2021-04-30 removed excom
2021-06-20 fixed concatenation syntax in motor controller
2021-07-02 cleaned up assembler source
2021-08-28 updated resources
2021-10-08 cleaned up assembler.py
2021-10-10 updated workflow diagram
2021-10-21 fixed bugs in assembler
2021-10-21 added .ds directive
2021-11-01 fixed error in isa docs
2021-11-01 fixed diagram
2021-11-05 added syntax highlighting configuration file for Sublime Text
2021-11-05 updated highlighter
2021-12-20 working on interrupt controller
2021-12-21 working on pic
2021-12-21 fixed some bugs
2021-12-21 fixed memory map error
2021-12-21 fixed bugs in counter_timer.v
2021-12-21 pic should be working fine now
2021-12-21 updated asm programs to work with pic
2021-12-21 Cleaned up vga sync generation code
2021-12-21 fixed bug in counter.asm
2021-12-21 now have a shell program working with the screen
2021-12-22 working on cursor for shell
2021-12-22 cursor now working for shell
2021-12-22 improved v_shell
2021-12-23 scrolling working in the gpu
2021-12-23 scrolling working
2021-12-23 v_shell now main shell
2021-12-24 updated shell
2021-12-25 cleaned up some asm programs
2022-01-02 Moved from KiCad 5 to KiCad 6, and fixed bad organization
2022-01-02 cleaned up pcb stuff
2022-01-02 updated .gitignore
2022-01-02 cleaning up
2022-01-02 cleaned up kicad stuff
2022-01-03 cleaned up pcb location
2022-01-20 updated ISA docs
2022-01-25 updated touch draw isa
2022-01-26 fixed-up touch draw
2022-01-28 updated servo comments and adjusted for new servo
2022-01-28 fixed servo math
2022-03-25 added proper clock constraints
2022-08-02 fixed up assembler
2022-08-02 update shell
2022-09-01 updated Makefile
2023-02-07 Update pic.v
    fixed addressing issue
2023-03-16 updated to KiCad 7
2023-04-23 now use a struct array for commands. maybe change the cpu to add indirect call sometime...
2023-04-23 shell restructured
2023-04-24 fixed issues with shell
2023-04-24 cleaned up shell
2023-04-25 touched up the shell
2023-04-25 updated sonar rtl. something is up with the first reading. I don't think it is the rtl. My guess is that the module might have to be pinged once to settle. not sure however.
2023-06-23 parameterizing for F_CPU
2023-06-24 parameterizing servo
2023-06-24 parameterized stuff
2023-06-24 parameterizing stuff
2023-06-24 added note to uart.v
2023-11-08 adding memory map info
2023-11-08 typo fixed
2023-11-09 modified memory map, README mem map is bad now
2023-11-12 fixed serious flaw with parameterization of motor controller
2024-03-16 added char handling
2024-05-25 updated to kicad 8
